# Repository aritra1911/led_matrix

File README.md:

# 8x8 LED Matrix
## Description
This uses a MAX7219, hence refer to its [datasheet](https://datasheets.maximintegrated.com/en/ds/MAX7219-MAX7221.pdf)
for interfacing.

In collaboration with [@CodeOn-ArK](https://github.com/CodeOn-ArK).

## Schematic

## Renders
### Front

### Back

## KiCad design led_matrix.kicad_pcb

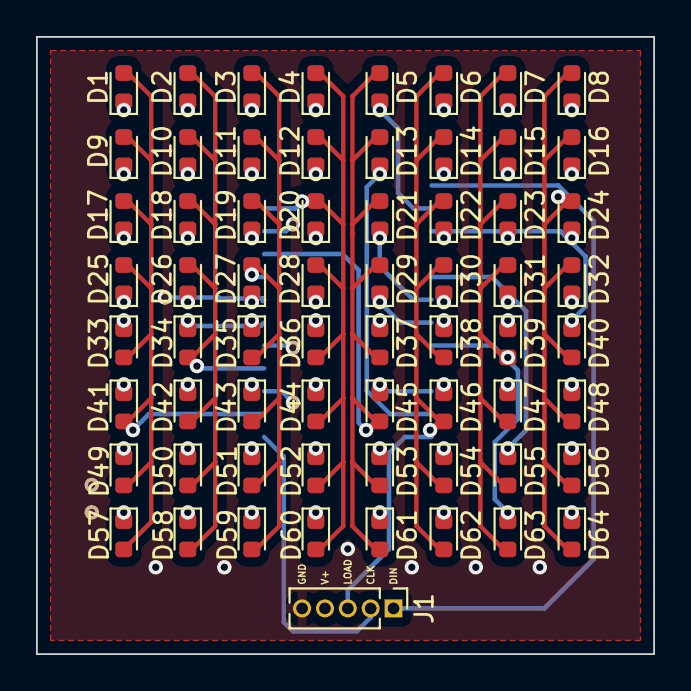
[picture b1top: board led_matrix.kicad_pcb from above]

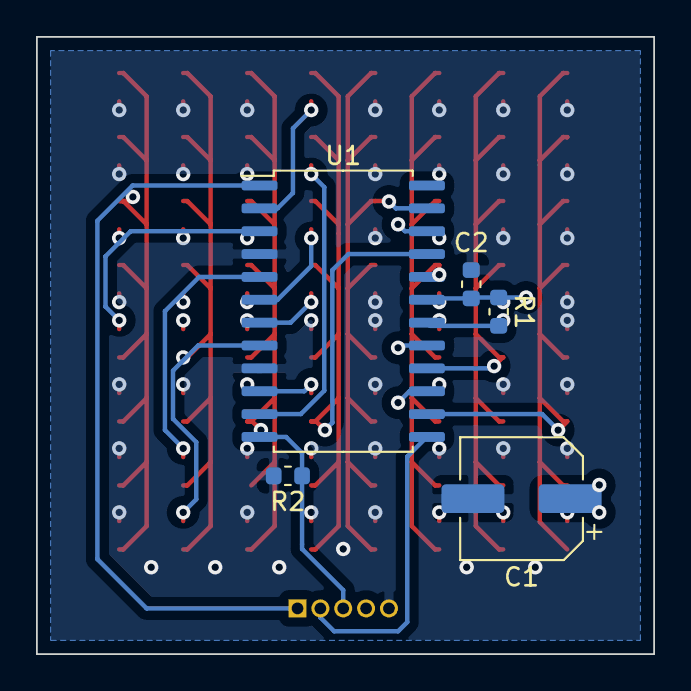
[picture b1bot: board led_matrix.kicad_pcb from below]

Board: 4 copper layers, 34.3 x 34.3 mm, 70 parts (5 on the bottom side), 22 nets.

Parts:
C1: 10uF; CP_Elec_6.3x3
C2: 100nF; C_0603_1608Metric
D1, D2, D3, D4, D5, D6, D7, D8, D9, D10, D11, D12, D13, D14, D15, D16, D17, D18, D19, D20, D21, D22, D23, D24, D25, D26, D27, D28, D29, D30, D31, D32, D33, D34, D35, D36, D37, D38, D39, D40, D41, D42, D43, D44, D45, D46, D47, D48, D49, D50, D51, D52, D53, D54, D55, D56, D57, D58, D59, D60, D61, D62, D63, D64: LED; LED_0603_1608Metric
J1: Conn_01x05_Male; PinHeader_1x05_P1.27mm_Vertical
R1: 27k; R_0603_1608Metric
R2: 10k; R_0603_1608Metric
U1: MAX7219; SOP-24_7.5x15.4mm_P1.27mm

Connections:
+5V: C1.1, C2.1, J1.4, R1.1, U1.19
/matc0: D1.2, D9.2, D17.2, D25.2, D33.2, D41.2, D49.2, D57.2, U1.14
/matc1: D2.2, D10.2, D18.2, D26.2, D34.2, D42.2, D50.2, D58.2, U1.16
/matc2: D3.2, D11.2, D19.2, D27.2, D35.2, D43.2, D51.2, D59.2, U1.20
/matc3: D4.2, D12.2, D20.2, D28.2, D36.2, D44.2, D52.2, D60.2, U1.23
/matc4: D5.2, D13.2, D21.2, D29.2, D37.2, D45.2, D53.2, D61.2, U1.21
/matc5: D6.2, D14.2, D22.2, D30.2, D38.2, D46.2, D54.2, D62.2, U1.15
/matc6: D7.2, D15.2, D23.2, D31.2, D39.2, D47.2, D55.2, D63.2, U1.17
/matc7: D8.2, D16.2, D24.2, D32.2, D40.2, D48.2, D56.2, D64.2, U1.22
/matr0: D1.1, D2.1, D3.1, D4.1, D5.1, D6.1, D7.1, D8.1, U1.2
/matr1: D9.1, D10.1, D11.1, D12.1, D13.1, D14.1, D15.1, D16.1, U1.11
/matr2: D17.1, D18.1, D19.1, D20.1, D21.1, D22.1, D23.1, D24.1, U1.6
/matr3: D25.1, D26.1, D27.1, D28.1, D29.1, D30.1, D31.1, D32.1, U1.7
/matr4: D33.1, D34.1, D35.1, D36.1, D37.1, D38.1, D39.1, D40.1, U1.3
/matr5: D41.1, D42.1, D43.1, D44.1, D45.1, D46.1, D47.1, D48.1, U1.10
/matr6: D49.1, D50.1, D51.1, D52.1, D53.1, D54.1, D55.1, D56.1, U1.5
/matr7: D57.1, D58.1, D59.1, D60.1, D61.1, D62.1, D63.1, D64.1, U1.8
CLK: J1.2, U1.13
DIN: J1.1, U1.1
GND: C1.2, C2.2, J1.5, R2.2, U1.4, U1.9
LOAD: J1.3, R2.1, U1.12
unnamed: R1.2, U1.18

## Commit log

2020-09-22 Initial Commit: Rev A
2020-09-22 Upgrade Rev A to Rev B
2020-09-22 Bump to Rev C.
2020-09-23 Update project file
2020-09-23 Finish Rev C PCB
2020-09-25 Upgrade to 4 Layer PCB
2020-09-25 Fix render previews in README.md
2020-09-25 Update PCB zone fills
